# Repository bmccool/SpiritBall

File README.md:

---
tags: 📝️/🌱️
aliases:
  -
cssclass:
---

# TITLE: [[SpiritBall]]
---
## Demo

## Abstract
With 100 days until Christmas 2022, this project is set as a design challenge to create a Christmas decoration to be handed out as gifts, and as an excuse to learn and play with new tech toys and concepts.  This Readme is a copy of my notebook for this project.
## MOC
[[ESP32-S3]]
[[SpiritBall]]
[[KiCad]]
[[ESP Flasher]]
## Project Idea
- A Christmas ornament, or other holiday decoration in a ball form with addressable or patterned LED lighting.
- Primarily designed to be hung from a tree branch (plug in to light strand?)
- Based on [[ws812b]] LEDs.  
- Designed around multiple interlocking "leaves" and central management core.
	- See pic
		- 

## Design
### Mechanical
- Using the "multiple interlocking "leaves" strategy
	- Can we utilize card edge connectors?
	- Simpler, we could just leave the traces uncovered and solder bridge them together.
	- LEDs will be placed along the edge, firing normal to the leaf face.
		- First pass, only on one side, we can think about adding a second set on the reverse side later
		- LEDs should fire primarily in the direction of the next leaf, which should help with light diffusion
	- Do we need additional diffusion?
		- Likely not, given the LEDs will shine into the next leaf *AND* the abiliity of software to dim the LEDs, we shouldn't need mechanical diffusion
### Electrical
- Use a [[WS2812B]] [[SMD LEDs|LED]]
	- Likely this one, which I think is the same as on the ESP32-S3 Dev board
	- [WS2812B-Mini](https://jlcpcb.com/partdetail/Worldsemi-WS2812BMini/C527089)
	- Alternatively, this one which is the normal [[WS2812B]]
	- [WS2812B](https://jlcpcb.com/partdetail/Worldsemi-WS2812B_BW/C2761795)
- Control LEDs with [ESP32-S3 Module](https://jlcpcb.com/partdetail/3198296-ESP32_S3_WROOM_1N8/C2913198)
	- [Datasheet](https://www.espressif.com/sites/default/files/documentation/esp32-s3-wroom-1_wroom-1u_datasheet_en.pdf)
	- Likely need to spend some time figuring out how to use module standalone instead of on dev board
	- Can we power this from a standard christmas light strand?
		- How about a battery? 18650?
	- Technical things
		- EN/BOOT, Reset, Power On, UART/USB
			- A switch on EN would be a temporary contact to ground to reset the board, probably wanted on main board for a while
			- A siwtch on BOOT would allow the board to be reset into BOOTLOADER mode.  Which would then allow programming.  Assuming we are loading via USB/UART, which would otherwise control the EN and BOOT pins via transistors (see Automatic Bootloader for S3), we would never use this button.  Ergo, don't need it on board, we can pull a button (still not very useful) to the flash tool board to save space and parts.
			- So, onboard button for EN, no onboard button for BOOT, but we will utilize an external flash tool (usb/uart bridge) and we can stick a redundant EN button and BOOT button there.
			- In this scenario, we still need a pullup on EN.  BOOT can be left "floating" on the internal pullup.
- USB-C
	- [JLCPCB Link](https://jlcpcb.com/partdetail/Molex-1054500101/C134092)
	- [Molex Part](https://www.molex.com/molex/products/part-detail/io_connectors/1054500101)
	- [Molex Spec](https://www.molex.com/pdm_docs/ps/PS-105448-001-001.pdf)
	- USB/UART converter
### Software
## Work
- [[2022-09-26]] Created [SpiritBall Repo]() with first pass of schematic and PCB layout.  Tagging as [SpiritBall v0.1.0]()  This is intended as a minimum viable product with only a single plane of LEDs.  I still need to create board gerber files and run them through [[JLCPCB]] online tools to check for compatibility, as well as generate a BOM and place the order.
	- 
	- 
- [[2022-11-01]] - Success!  The first batch of 5 assembled boards came back last week (I had done some minor tocuch up work, swapped some parts for in-stock, etc).  I also used a [[ESP-Prog]] flash board to get things started, though I think I could eventually use the USB cable or even [[OTA]] updates.  **TODO** add pictures and video.  Re: software, I've been turned onto using [[RMT]] for controlling the LEDs by [[@Chris Lomont]], and it was a cinch to get up and running a simple rainbow chase.  Now the fun part - Making it look more appealing and less like rainbow unicorn vomit :) 
	- PS: Had a brief moment of panic - Playing with some LED patterns and decided to pull back the brightness so it didn't hurt my eyes.  I lowered the SATURATION when I meant to lower the VALUE in the HVS color representation.  This of course just made all the LEDs white, and full brightness, which spiked current draw up over 700mA.  Oops.  But the program runs at boot, and is powered through the PROG interface meant there wasn't enough power available to flash through UART.  Turns out the USB port on the [[SpiritBall]] works fine to power the board with some extra power.  Plugged in both USB and PROG interface (which saw maybe 10mA draw) and recovered the board.  I'm pretty happy with how this first revision is performing.
	- Also, had to shake off some rust to get example code up and running.  Here's what I did:
		```
		cd C:\projects\brendon\ESP32S3-Project-Template
		xcopy /e /i C:\Espressif\frameworks\esp-idf-v5.0\examples\get-started\hello_world ./
		idf.py set-target esp32s3
		(remove build dir if it complains)
		idf.py -p COM5 flash monitor
		```
- [[2022-11-05]] - I've been experimenting with different patterns and have got to the point I have things worth saving.  So I'm spending some time to update github.  Also switched over to C++ for most things, but I kept the [[RMT]] encoder in C because I didn't feel like re-writing it and it works well enough as is... Maybe that's a task for a later date.  Things I still need to do:
	- [ ] Settle on a handful of set patterns (including `OFF`)
	- [ ] Cycle through set patterns with onboard buttons
	- [ ] Add some sort of software over-current protection
	- [ ] Update via USB-C cable
	- [ ] Update via OTA (stretch)
	- [ ] Control patterns via BT or WiFi (stretch)

/Work
# ./[[SpiritBall]]
---

Tags: [[ESP32-S3]]

Reference:

Related:

Created: [[2022-09-16]]

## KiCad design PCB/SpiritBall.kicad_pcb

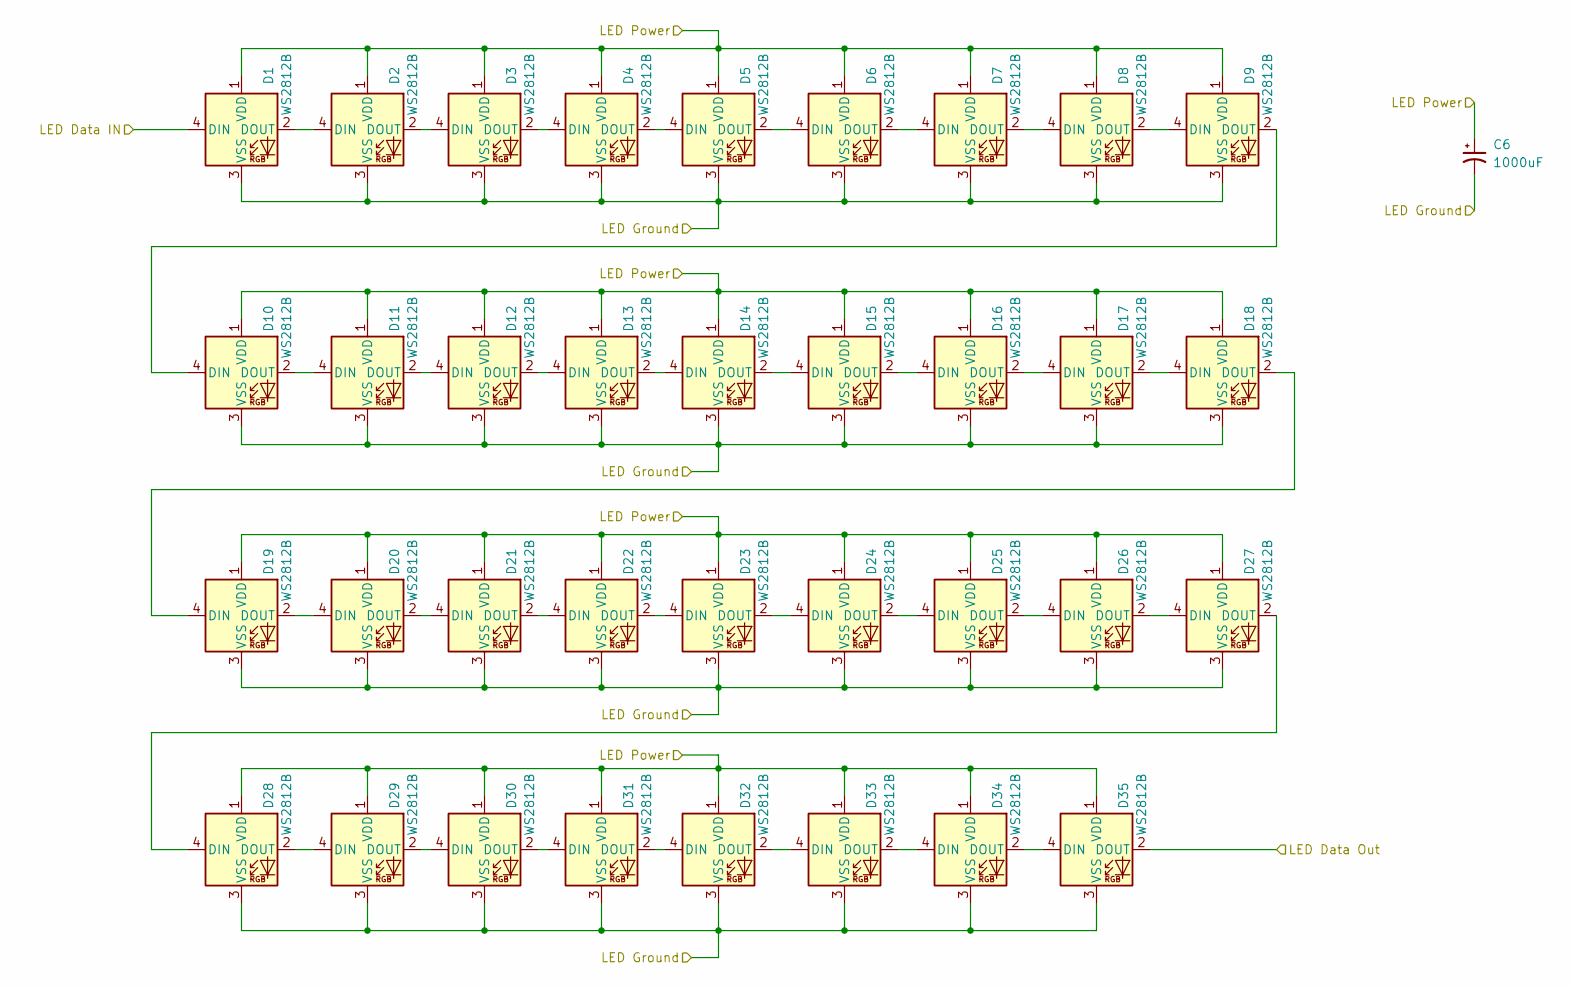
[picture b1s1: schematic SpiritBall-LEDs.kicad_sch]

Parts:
C6: 1000uF; C_Elec_8x10.2
D1, D2, D3, D4, D5, D6, D7, D8, D9, D10, D11, D12, D13, D14, D15, D16, D17, D18, D19, D20, D21, D22, D23, D24, D25, D26, D27, D28, D29, D30, D31, D32, D33, D34, D35: WS2812B; LED_WS2812B_PLCC4_5.0x5.0mm_P3.2mm

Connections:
+5V: C6.1, D1.1 (VDD), D2.1 (VDD), D3.1 (VDD), D4.1 (VDD), D5.1 (VDD), D6.1 (VDD), D7.1 (VDD), D8.1 (VDD), D9.1 (VDD), D10.1 (VDD), D11.1 (VDD), D12.1 (VDD), D13.1 (VDD), D14.1 (VDD), D15.1 (VDD), D16.1 (VDD), D17.1 (VDD), D18.1 (VDD), D19.1 (VDD), D20.1 (VDD), D21.1 (VDD), D22.1 (VDD), D23.1 (VDD), D24.1 (VDD), D25.1 (VDD), D26.1 (VDD), D27.1 (VDD), D28.1 (VDD), D29.1 (VDD), D30.1 (VDD), D31.1 (VDD), D32.1 (VDD), D33.1 (VDD), D34.1 (VDD), D35.1 (VDD); also elsewhere on the board
/ESP32-S3/LED Data: D1.4 (DIN); also elsewhere on the board
/LEDs/LED Data Out: D35.2 (DOUT)
GND: C6.2, D1.3 (VSS), D2.3 (VSS), D3.3 (VSS), D4.3 (VSS), D5.3 (VSS), D6.3 (VSS), D7.3 (VSS), D8.3 (VSS), D9.3 (VSS), D10.3 (VSS), D11.3 (VSS), D12.3 (VSS), D13.3 (VSS), D14.3 (VSS), D15.3 (VSS), D16.3 (VSS), D17.3 (VSS), D18.3 (VSS), D19.3 (VSS), D20.3 (VSS), D21.3 (VSS), D22.3 (VSS), D23.3 (VSS), D24.3 (VSS), D25.3 (VSS), D26.3 (VSS), D27.3 (VSS), D28.3 (VSS), D29.3 (VSS), D30.3 (VSS), D31.3 (VSS), D32.3 (VSS), D33.3 (VSS), D34.3 (VSS), D35.3 (VSS); also elsewhere on the board
unnamed: D1.2 (DOUT), D2.4 (DIN)
unnamed: D2.2 (DOUT), D3.4 (DIN)
unnamed: D3.2 (DOUT), D4.4 (DIN)
unnamed: D4.2 (DOUT), D5.4 (DIN)
unnamed: D5.2 (DOUT), D6.4 (DIN)
unnamed: D6.2 (DOUT), D7.4 (DIN)
unnamed: D7.2 (DOUT), D8.4 (DIN)
unnamed: D8.2 (DOUT), D9.4 (DIN)
unnamed: D10.2 (DOUT), D11.4 (DIN)
unnamed: D9.2 (DOUT), D10.4 (DIN)
unnamed: D11.2 (DOUT), D12.4 (DIN)
unnamed: D12.2 (DOUT), D13.4 (DIN)
unnamed: D13.2 (DOUT), D14.4 (DIN)
unnamed: D14.2 (DOUT), D15.4 (DIN)
unnamed: D15.2 (DOUT), D16.4 (DIN)
unnamed: D16.2 (DOUT), D17.4 (DIN)
unnamed: D17.2 (DOUT), D18.4 (DIN)
unnamed: D18.2 (DOUT), D19.4 (DIN)
unnamed: D19.2 (DOUT), D20.4 (DIN)
unnamed: D20.2 (DOUT), D21.4 (DIN)
unnamed: D21.2 (DOUT), D22.4 (DIN)
unnamed: D22.2 (DOUT), D23.4 (DIN)
unnamed: D23.2 (DOUT), D24.4 (DIN)
unnamed: D24.2 (DOUT), D25.4 (DIN)
unnamed: D25.2 (DOUT), D26.4 (DIN)
unnamed: D26.2 (DOUT), D27.4 (DIN)
unnamed: D27.2 (DOUT), D28.4 (DIN)
unnamed: D28.2 (DOUT), D29.4 (DIN)
unnamed: D29.2 (DOUT), D30.4 (DIN)
unnamed: D30.2 (DOUT), D31.4 (DIN)
unnamed: D31.2 (DOUT), D32.4 (DIN)
unnamed: D32.2 (DOUT), D33.4 (DIN)
unnamed: D33.2 (DOUT), D34.4 (DIN)
unnamed: D34.2 (DOUT), D35.4 (DIN)

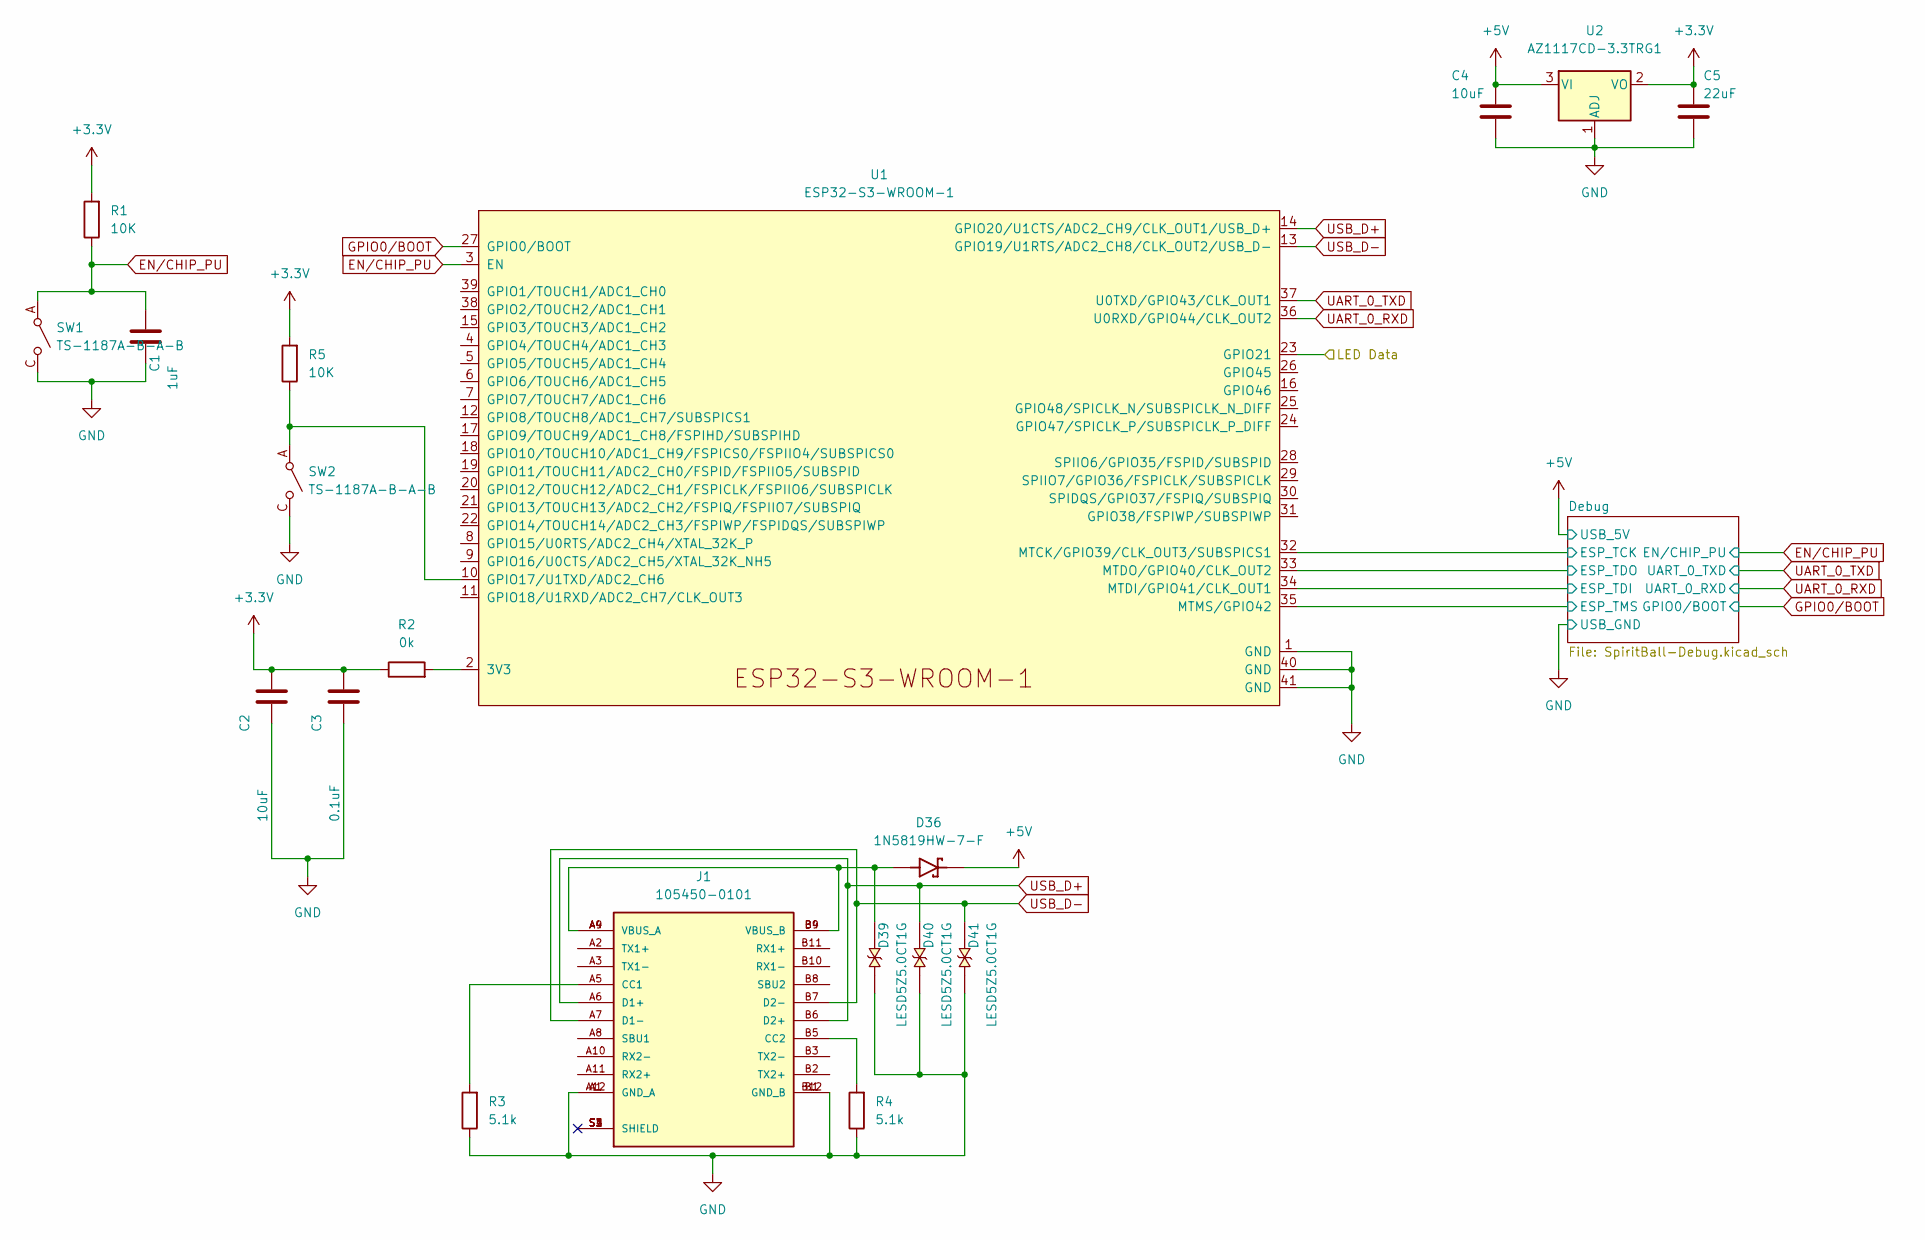
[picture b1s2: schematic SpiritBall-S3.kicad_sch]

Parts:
C1: 1uF; C_0402_1005Metric
C2, C4: 10uF; C_0402_1005Metric
C3: 0.1uF; C_0402_1005Metric
C5: 22uF; C_0402_1005Metric
D36: 1N5819HW-7-F; D_SOD-123; PARTREV 18-2
D39, D40, D41: LESD5Z5.0CT1G; D_SOD-523; PARTREV O
J1: 105450-0101; USB_C_MOLEX_105450-0101; PARTREV A7
R1, R5: 10K; R_0402_1005Metric
R2: 0k; R_0402_1005Metric
R3, R4: 5.1k; R_0402_1005Metric
SW1, SW2: TS-1187A-B-A-B; SW_TS-1187A-B-A-B
U1: ESP32-S3-WROOM-1
U2: AZ1117CD-3.3TRG1; TO-252-2

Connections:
+3.3V: C2.1, C3.1, C5.1, R1.2, R2.1, R5.2, U2.2 (VO)
+5V: C4.1, D36.1, U2.3 (VI); also elsewhere on the board
/ESP32-S3/Debug/ESP_TCK: U1.32 (MTCK/GPIO39/CLK_OUT3/SUBSPICS1); also elsewhere on the board
/ESP32-S3/Debug/ESP_TDI: U1.34 (MTDI/GPIO41/CLK_OUT1); also elsewhere on the board
/ESP32-S3/Debug/ESP_TDO: U1.33 (MTDO/GPIO40/CLK_OUT2); also elsewhere on the board
/ESP32-S3/Debug/ESP_TMS: U1.35 (MTMS/GPIO42); also elsewhere on the board
/ESP32-S3/LED Data: U1.23 (GPIO21); also elsewhere on the board
EN/CHIP_PU: C1.1, R1.1, SW1.A, SW1.B, U1.3 (EN); also elsewhere on the board
GND: C1.2, C2.2, C3.2, C4.2, C5.2, D39.1, D40.1, D41.1, J1.A1 (GND_A), J1.A12 (GND_A), J1.B1 (GND_B), J1.B12 (GND_B), R3.1, R4.1, SW1.C, SW1.D, SW2.C, SW2.D, U1.1 (GND), U1.40 (GND), U1.41 (GND), U2.1 (ADJ); also elsewhere on the board
GPIO0/BOOT: U1.27 (GPIO0/BOOT); also elsewhere on the board
unnamed: D36.2, D39.2, J1.A4 (VBUS_A), J1.A9 (VBUS_A), J1.B4 (VBUS_B), J1.B9 (VBUS_B)
unnamed: J1.A5 (CC1), R3.2
unnamed: J1.B5 (CC2), R4.2
unnamed: R2.2, U1.2 (3V3)
unnamed: R5.1, SW2.A, SW2.B, U1.10 (GPIO17/U1TXD/ADC2_CH6)
UART_0_RXD: U1.36 (U0RXD/GPIO44/CLK_OUT2); also elsewhere on the board
UART_0_TXD: U1.37 (U0TXD/GPIO43/CLK_OUT1); also elsewhere on the board
USB_D+: D40.2, J1.A6 (D1+), J1.B6 (D2+), U1.14 (GPIO20/U1CTS/ADC2_CH9/CLK_OUT1/USB_D+)
USB_D-: D41.2, J1.A7 (D1-), J1.B7 (D2-), U1.13 (GPIO19/U1RTS/ADC2_CH8/CLK_OUT2/USB_D-)

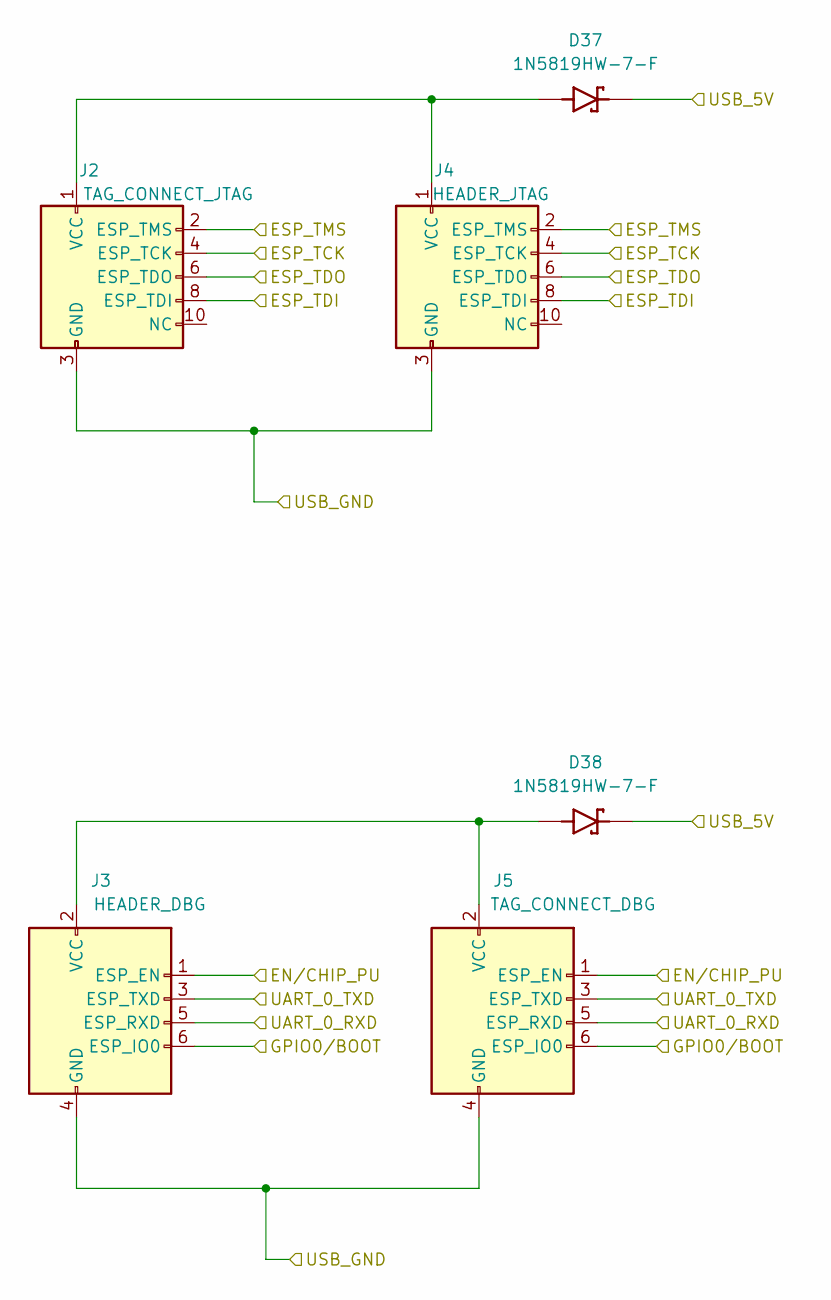
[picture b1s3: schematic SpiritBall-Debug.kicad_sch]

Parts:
D37, D38: 1N5819HW-7-F; D_SOD-123; PARTREV 18-2
J2: TAG_CONNECT_JTAG; Tag-Connect_TC2050-IDC-FP_2x05_P1.27mm_Vertical
J3: HEADER_DBG; PinHeader_2x03_P1.27mm_Vertical
J4: HEADER_JTAG; PinHeader_2x05_P1.27mm_Vertical
J5: TAG_CONNECT_DBG; Tag-Connect_TC2030-IDC-FP_2x03_P1.27mm_Vertical

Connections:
+5V: D37.1, D38.1; also elsewhere on the board
/ESP32-S3/Debug/ESP_TCK: J2.4 (ESP_TCK), J4.4 (ESP_TCK); also elsewhere on the board
/ESP32-S3/Debug/ESP_TDI: J2.8 (ESP_TDI), J4.8 (ESP_TDI); also elsewhere on the board
/ESP32-S3/Debug/ESP_TDO: J2.6 (ESP_TDO), J4.6 (ESP_TDO); also elsewhere on the board
/ESP32-S3/Debug/ESP_TMS: J2.2 (ESP_TMS), J4.2 (ESP_TMS); also elsewhere on the board
EN/CHIP_PU: J3.1 (ESP_EN), J5.1 (ESP_EN); also elsewhere on the board
GND: J2.3 (GND), J2.5 (GND), J2.7 (GND), J2.9 (GND), J3.4 (GND), J4.3 (GND), J4.5 (GND), J4.7 (GND), J4.9 (GND), J5.4 (GND); also elsewhere on the board
GPIO0/BOOT: J3.6 (ESP_IO0), J5.6 (ESP_IO0); also elsewhere on the board
unnamed: D37.2, J2.1 (VCC), J4.1 (VCC)
unnamed: D38.2, J3.2 (VCC), J5.2 (VCC)
UART_0_RXD: J3.5 (ESP_RXD), J5.5 (ESP_RXD); also elsewhere on the board
UART_0_TXD: J3.3 (ESP_TXD), J5.3 (ESP_TXD); also elsewhere on the board

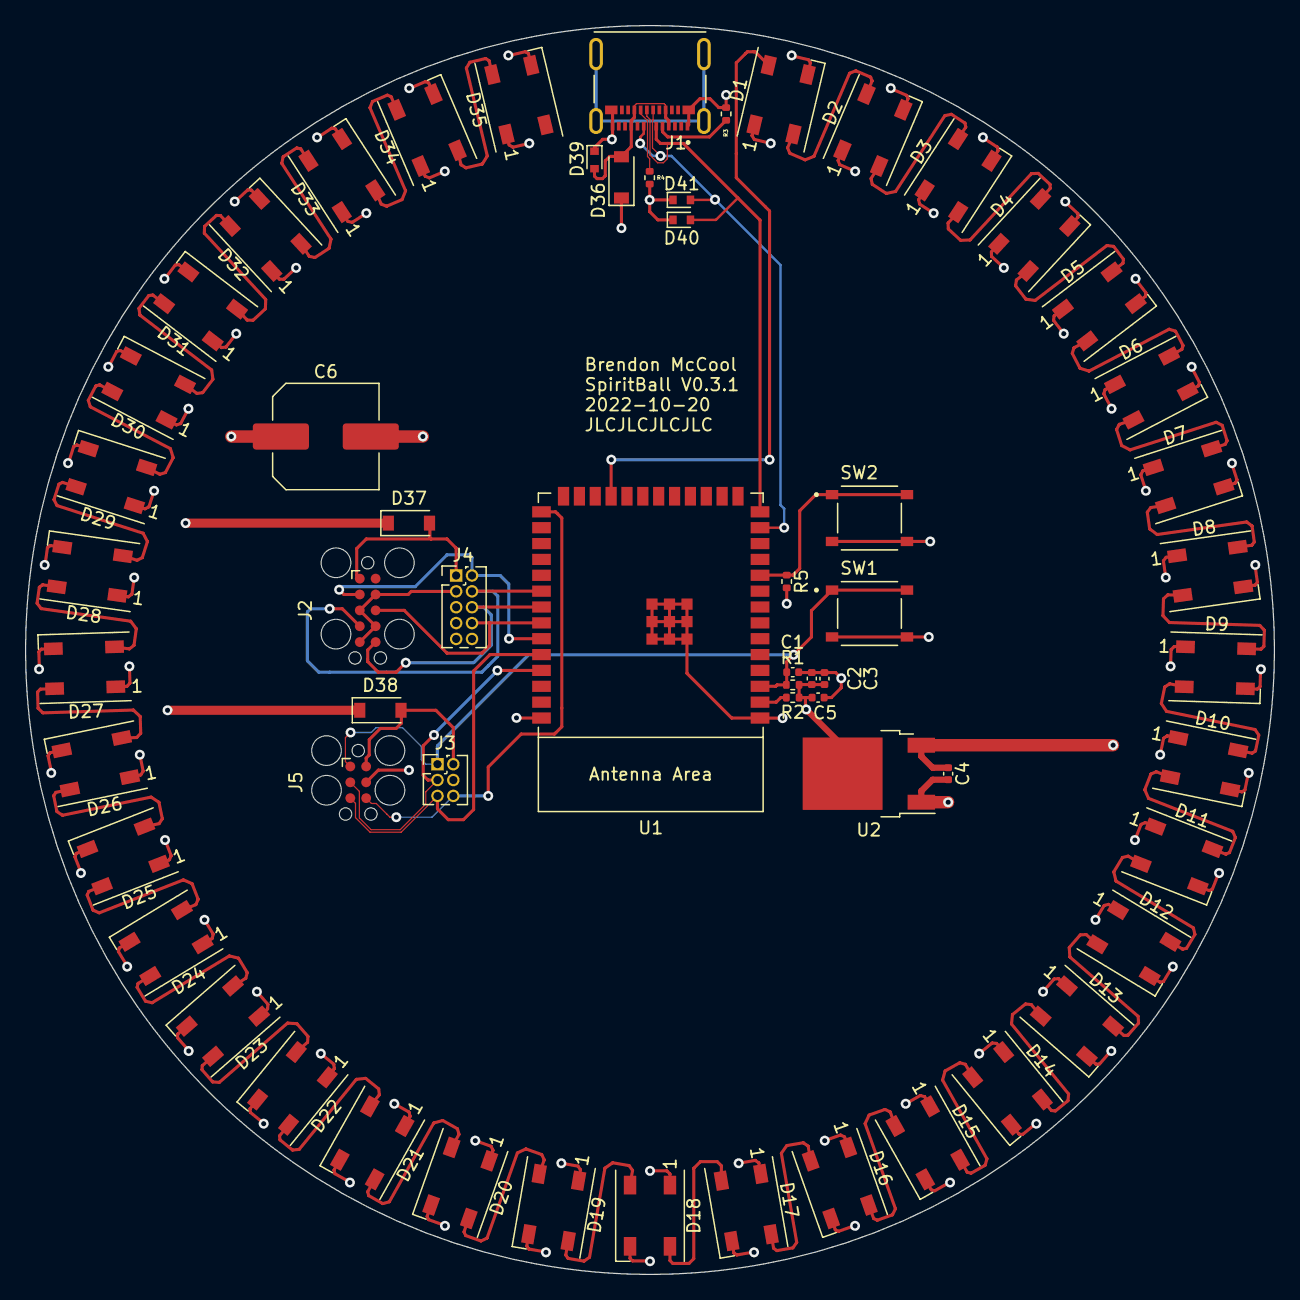
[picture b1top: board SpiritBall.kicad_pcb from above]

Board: 4 copper layers, 100.0 x 100.0 mm, 61 parts (0 on the bottom side), 55 nets.

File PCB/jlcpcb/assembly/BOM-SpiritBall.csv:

Comment,Designator,Footprint,LCSC
105450-0101,J1,USB_C_MOLEX_105450-0101,C134092
LESD5Z5.0CT1G,"D39,D40,D41",D_SOD-523,C136167
0.1uF,C3,C_0402_1005Metric,C1525
10uF,"C2,C4",C_0402_1005Metric,C15525
0k,R2,R_0402_1005Metric,C17168
10K,"R1,R5",R_0402_1005Metric,C25744
5.1k,"R3,R4",R_0402_1005Metric,C25905
WS2812B,"D1,D10,D11,D12,D13,D14,D15,D16,D17,D18,D19,D2,D20,D21,D22,D23,D24,D25,D26,D27,D28,D29,D3,D30,D31,D32,D33,D34,D35,D4,D5,D6,D7,D8,D9",LED_WS2812B_PLCC4_5.0x5.0mm_P3.2mm,C2843785
ESP32-S3-WROOM-1,U1,ESP32-S3-WROOM-1,C2913204
TS-1187A-B-A-B,"SW1,SW2",SW_TS-1187A-B-A-B,C318884
22uF,C5,C_0402_1005Metric,C415703
AZ1117CD-3.3TRG1,U2,TO-252-2,C460427
1uF,C1,C_0402_1005Metric,C52923
1N5819HW-7-F,"D36,D37,D38",D_SOD-123,C82544
1000uF,C6,C_Elec_8x10.2,C99833
TAG_CONNECT_DBG,J5,Tag-Connect_TC2030-IDC-FP_2x03_P1.27mm_Vertical,
TAG_CONNECT_JTAG,J2,Tag-Connect_TC2050-IDC-FP_2x05_P1.27mm_Vertical,
HEADER_DBG,J3,PinHeader_2x03_P1.27mm_Vertical,
HEADER_JTAG,J4,PinHeader_2x05_P1.27mm_Vertical,

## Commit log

2022-09-26 Add readme, move pcb files to subfolder
2022-10-21 Version 0.3.0, sent for fabrication
2022-11-05 Pull in source code
2022-11-06 Add color names
2022-11-08 Add button, two total patterns
2022-11-08 Add glow pattern
2022-11-11 Add chase
2022-11-18 Add more patterns
2023-08-02 Fix compilation
